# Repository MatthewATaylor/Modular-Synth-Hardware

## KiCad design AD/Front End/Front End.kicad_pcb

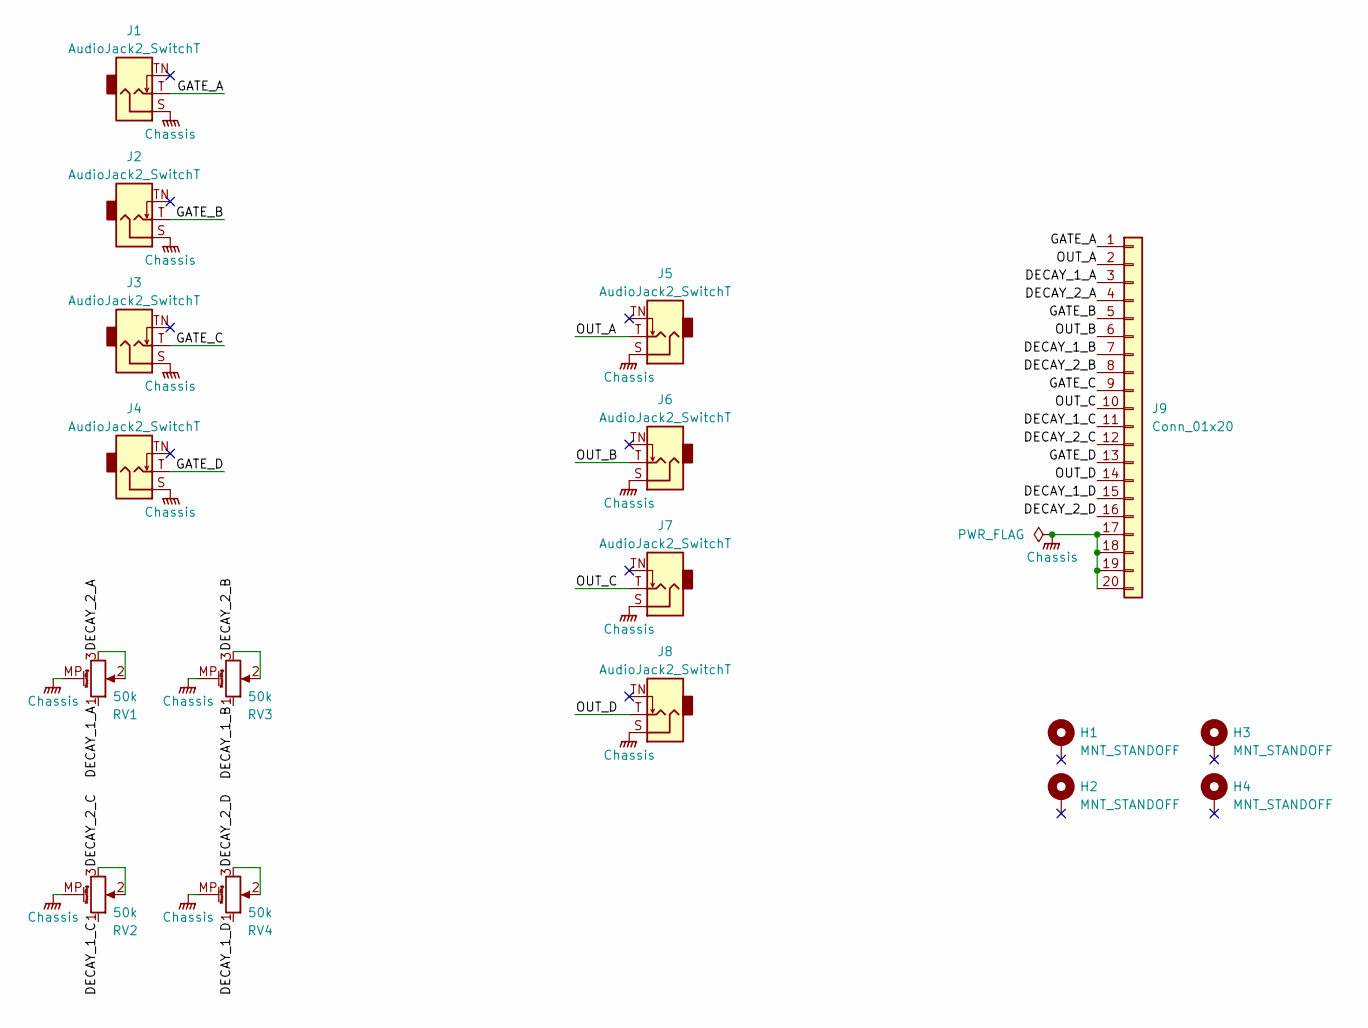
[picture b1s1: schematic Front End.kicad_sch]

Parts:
H1, H2, H3, H4: MNT_STANDOFF; MountingHole_Pitch7.5mm_Drill3.4mm
J1, J2, J3, J4, J5, J6, J7, J8: AudioJack2_SwitchT; Jack_3.5mm_QingPu_WQP-PJ398SM_Vertical_CircularHoles
J9: Conn_01x20; PinSocket_1x20_P2.54mm_Vertical
RV1, RV2, RV3, RV4: 50k; Potentiometer_Alpha_RD901F-40-00D_Single_Vertical_MP

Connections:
/DECAY_1_A: J9.3, RV1.1
/DECAY_1_B: J9.7, RV3.1
/DECAY_1_C: J9.11, RV2.1
/DECAY_1_D: J9.15, RV4.1
/DECAY_2_A: J9.4, RV1.2, RV1.3
/DECAY_2_B: J9.8, RV3.2, RV3.3
/DECAY_2_C: J9.12, RV2.2, RV2.3
/DECAY_2_D: J9.16, RV4.2, RV4.3
/GATE_A: J1.T, J9.1
/GATE_B: J2.T, J9.5
/GATE_C: J3.T, J9.9
/GATE_D: J4.T, J9.13
/OUT_A: J5.T, J9.2
/OUT_B: J6.T, J9.6
/OUT_C: J7.T, J9.10
/OUT_D: J8.T, J9.14
Chassis: J1.S, J2.S, J3.S, J4.S, J5.S, J6.S, J7.S, J8.S, J9.17, J9.18, J9.19, J9.20, RV1.MP (MountPin), RV2.MP (MountPin), RV3.MP (MountPin), RV4.MP (MountPin)

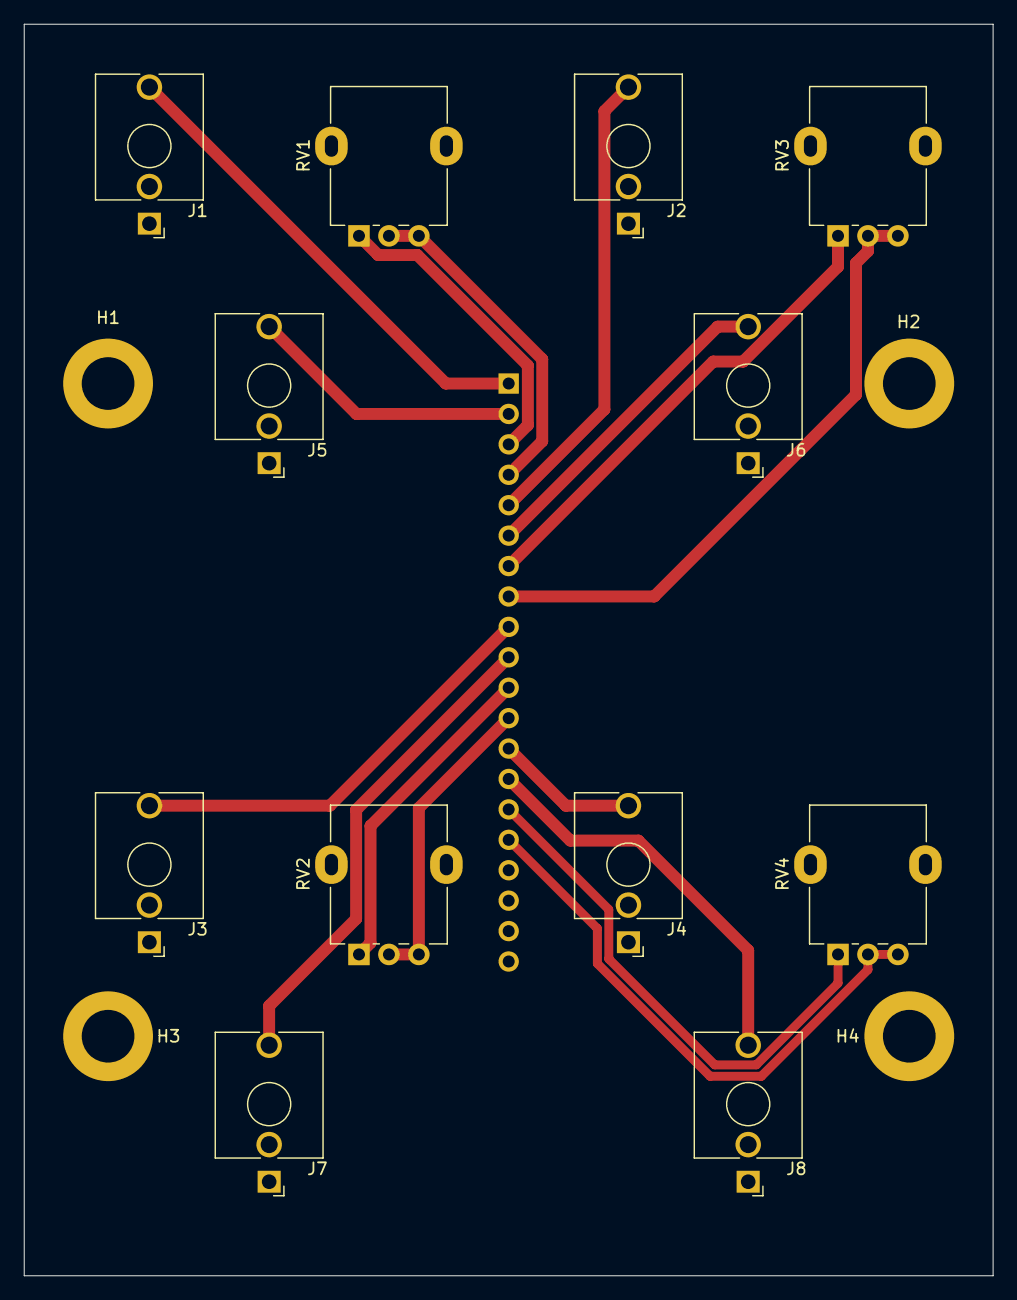
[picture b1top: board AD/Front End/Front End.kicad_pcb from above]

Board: 2 copper layers, 80.9 x 104.5 mm, 17 parts (1 on the bottom side), 17 nets.

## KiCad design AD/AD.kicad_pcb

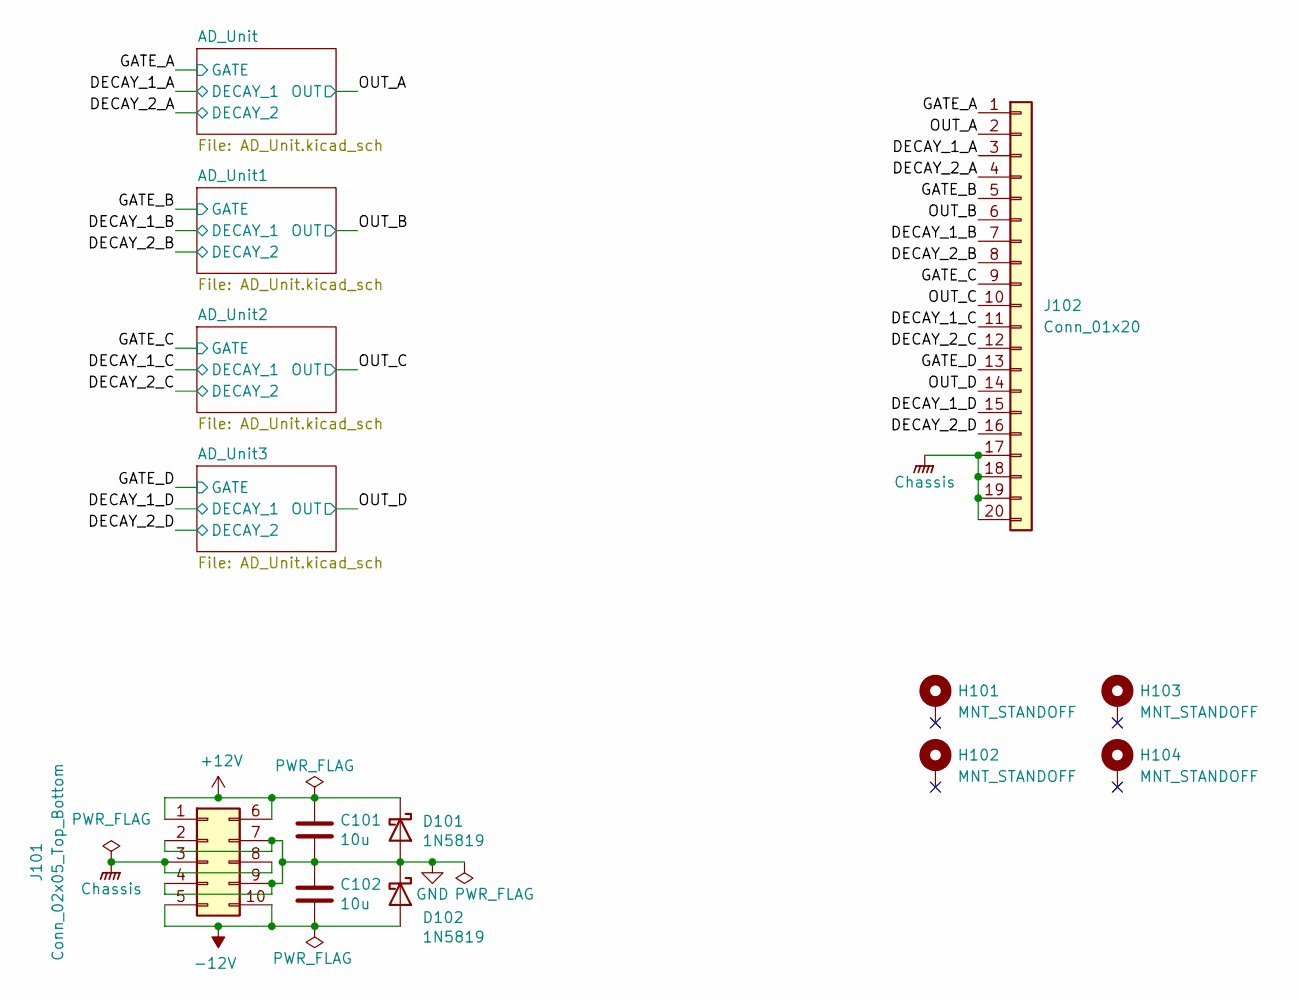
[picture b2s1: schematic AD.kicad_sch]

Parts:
C101, C102: 10u; C_Disc_D5.5mm_W4.0mm_P2.50mm
D101, D102: 1N5819; D_DO-41_SOD81_P10.16mm_Horizontal
H101, H102, H103, H104: MNT_STANDOFF; MountingHole_Pitch7.5mm_Drill3.4mm
J101: Conn_02x05_Top_Bottom; Molex_Mini-Fit_Jr_5566-10A_2x05_P4.20mm_Vertical
J102: Conn_01x20; PinHeader_1x20_P2.54mm_Vertical

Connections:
+12V: C101.1, D101.1 (K), J101.1, J101.6; also elsewhere on the board
-12V: C102.2, D102.2 (A), J101.5, J101.10
/DECAY_1_A: J102.3; also elsewhere on the board
/DECAY_1_B: J102.7; also elsewhere on the board
/DECAY_1_C: J102.11; also elsewhere on the board
/DECAY_1_D: J102.15; also elsewhere on the board
/DECAY_2_A: J102.4; also elsewhere on the board
/DECAY_2_B: J102.8; also elsewhere on the board
/DECAY_2_C: J102.12; also elsewhere on the board
/DECAY_2_D: J102.16; also elsewhere on the board
/GATE_A: J102.1; also elsewhere on the board
/GATE_B: J102.5; also elsewhere on the board
/GATE_C: J102.9; also elsewhere on the board
/GATE_D: J102.13; also elsewhere on the board
/OUT_A: J102.2; also elsewhere on the board
/OUT_B: J102.6; also elsewhere on the board
/OUT_C: J102.10; also elsewhere on the board
/OUT_D: J102.14; also elsewhere on the board
Chassis: J101.3, J101.8, J102.17, J102.18, J102.19, J102.20
GND: C101.2, C102.1, D101.2 (A), D102.1 (K), J101.2, J101.4, J101.7, J101.9; also elsewhere on the board

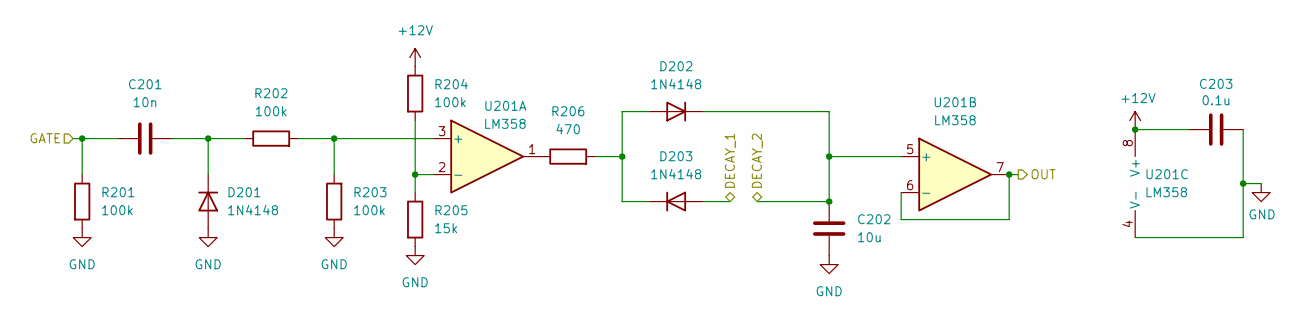
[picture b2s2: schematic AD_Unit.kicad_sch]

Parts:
C201: 10n; C_Disc_D5.5mm_W2.5mm_P2.50mm
C202: 10u; C_Disc_D5.5mm_W4.0mm_P2.50mm
C203: 0.1u; C_Disc_D5.5mm_W2.5mm_P2.50mm
D201, D202, D203: 1N4148; D_DO-35_SOD27_P7.62mm_Horizontal
R201, R202, R203, R204: 100k; R_Axial_DIN0207_L6.3mm_D2.5mm_P7.62mm_Horizontal
R205: 15k; R_Axial_DIN0207_L6.3mm_D2.5mm_P7.62mm_Horizontal
R206: 470; R_Axial_DIN0207_L6.3mm_D2.5mm_P7.62mm_Horizontal
U201: LM358; DIP-8_W7.62mm_Socket

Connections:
+12V: C203.1, R204.1, U201.8 (V+); also elsewhere on the board
/DECAY_1_A: D203.2 (A); also elsewhere on the board
/DECAY_2_A: C202.1, D202.1 (K), U201.5 (+); also elsewhere on the board
/GATE_A: C201.1, R201.1; also elsewhere on the board
/OUT_A: U201.6 (-), U201.7; also elsewhere on the board
GND: C202.2, C203.2, D201.2 (A), R201.2, R203.1, R205.2, U201.4 (V-); also elsewhere on the board
unnamed: C201.2, D201.1 (K), R202.1
unnamed: D202.2 (A), D203.1 (K), R206.2
unnamed: R206.1, U201.1
unnamed: R202.2, R203.2, U201.3 (+)
unnamed: R204.2, R205.1, U201.2 (-)

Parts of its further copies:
C401, C701, C901: 10n; C_Disc_D5.5mm_W2.5mm_P2.50mm
C402, C702, C902: 10u; C_Disc_D5.5mm_W4.0mm_P2.50mm
C403, C703, C903: 0.1u; C_Disc_D5.5mm_W2.5mm_P2.50mm
D401, D402, D403, D701, D702, D703, D901, D902, D903: 1N4148; D_DO-35_SOD27_P7.62mm_Horizontal
R401, R402, R403, R404, R701, R702, R703, R704, R901, R902, R903, R904: 100k; R_Axial_DIN0207_L6.3mm_D2.5mm_P7.62mm_Horizontal
R405, R705, R905: 15k; R_Axial_DIN0207_L6.3mm_D2.5mm_P7.62mm_Horizontal
R406, R706, R906: 470; R_Axial_DIN0207_L6.3mm_D2.5mm_P7.62mm_Horizontal
U401, U701, U901: LM358; DIP-8_W7.62mm_Socket

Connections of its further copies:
+12V: C403.1, C703.1, C903.1, R404.1, R704.1, R904.1, U401.8 (V+), U701.8 (V+), U901.8 (V+); also elsewhere on the board
/DECAY_1_B: D403.2 (A); also elsewhere on the board
/DECAY_1_C: D703.2 (A); also elsewhere on the board
/DECAY_1_D: D903.2 (A); also elsewhere on the board
/DECAY_2_B: C402.1, D402.1 (K), U401.5 (+); also elsewhere on the board
/DECAY_2_C: C702.1, D702.1 (K), U701.5 (+); also elsewhere on the board
/DECAY_2_D: C902.1, D902.1 (K), U901.5 (+); also elsewhere on the board
/GATE_B: C401.1, R401.1; also elsewhere on the board
/GATE_C: C701.1, R701.1; also elsewhere on the board
/GATE_D: C901.1, R901.1; also elsewhere on the board
/OUT_B: U401.6 (-), U401.7; also elsewhere on the board
/OUT_C: U701.6 (-), U701.7; also elsewhere on the board
/OUT_D: U901.6 (-), U901.7; also elsewhere on the board
GND: C402.2, C403.2, C702.2, C703.2, C902.2, C903.2, D401.2 (A), D701.2 (A), D901.2 (A), R401.2, R403.1, R405.2, R701.2, R703.1, R705.2, R901.2, R903.1, R905.2, U401.4 (V-), U701.4 (V-), U901.4 (V-); also elsewhere on the board
unnamed: C401.2, D401.1 (K), R402.1
unnamed: D402.2 (A), D403.1 (K), R406.2
unnamed: C701.2, D701.1 (K), R702.1
unnamed: D702.2 (A), D703.1 (K), R706.2
unnamed: C901.2, D901.1 (K), R902.1
unnamed: D902.2 (A), D903.1 (K), R906.2
unnamed: R406.1, U401.1
unnamed: R706.1, U701.1
unnamed: R906.1, U901.1
unnamed: R402.2, R403.2, U401.3 (+)
unnamed: R404.2, R405.1, U401.2 (-)
unnamed: R702.2, R703.2, U701.3 (+)
unnamed: R704.2, R705.1, U701.2 (-)
unnamed: R902.2, R903.2, U901.3 (+)
unnamed: R904.2, R905.1, U901.2 (-)

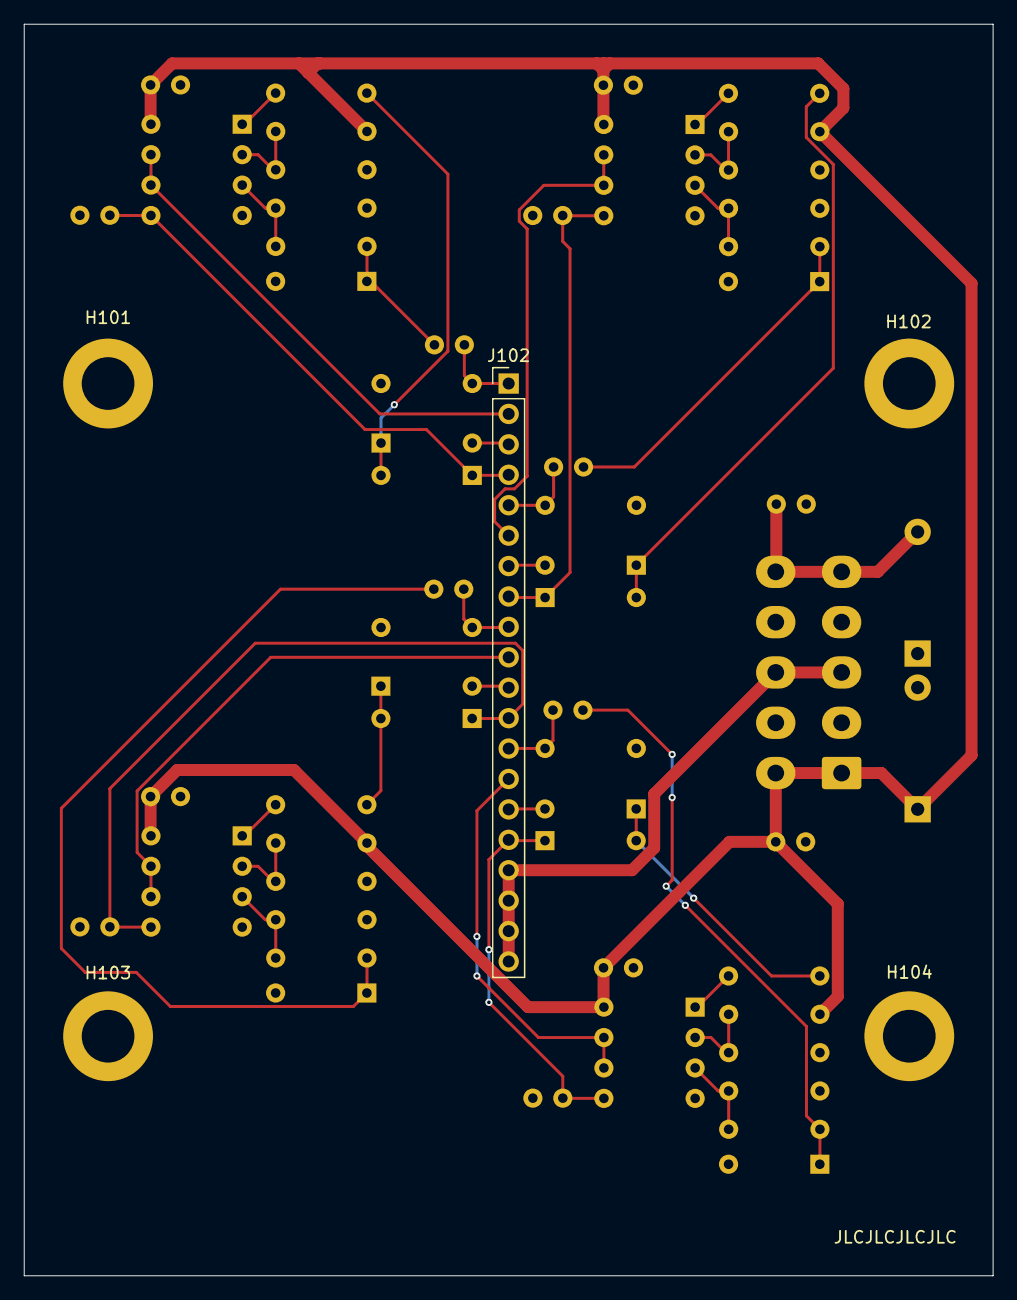
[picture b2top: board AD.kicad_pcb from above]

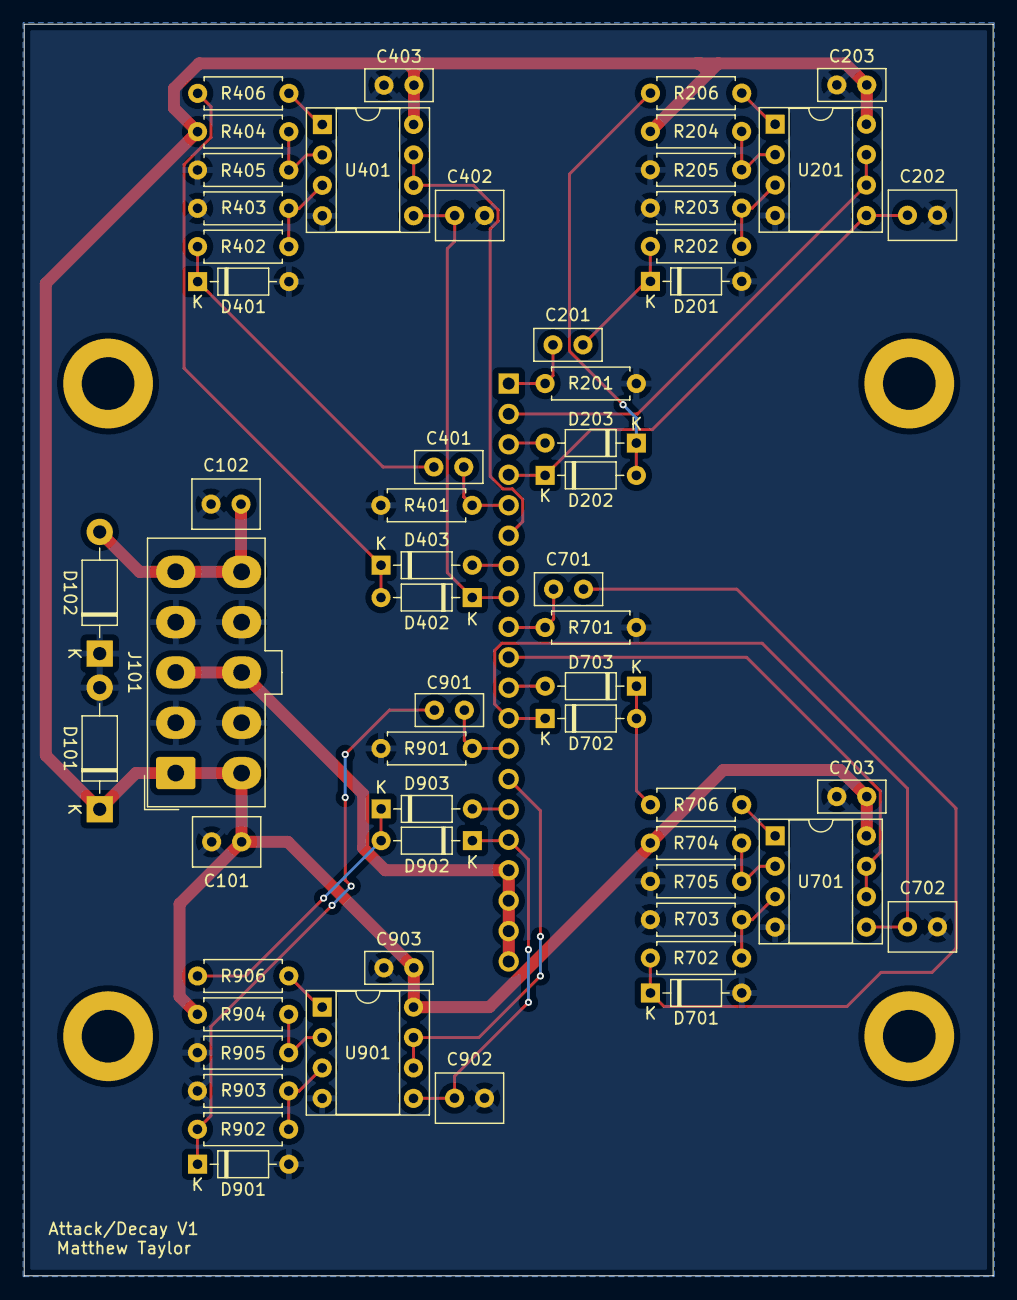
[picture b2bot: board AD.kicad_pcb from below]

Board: 2 copper layers, 80.9 x 104.5 mm, 62 parts (57 on the bottom side), 40 nets.

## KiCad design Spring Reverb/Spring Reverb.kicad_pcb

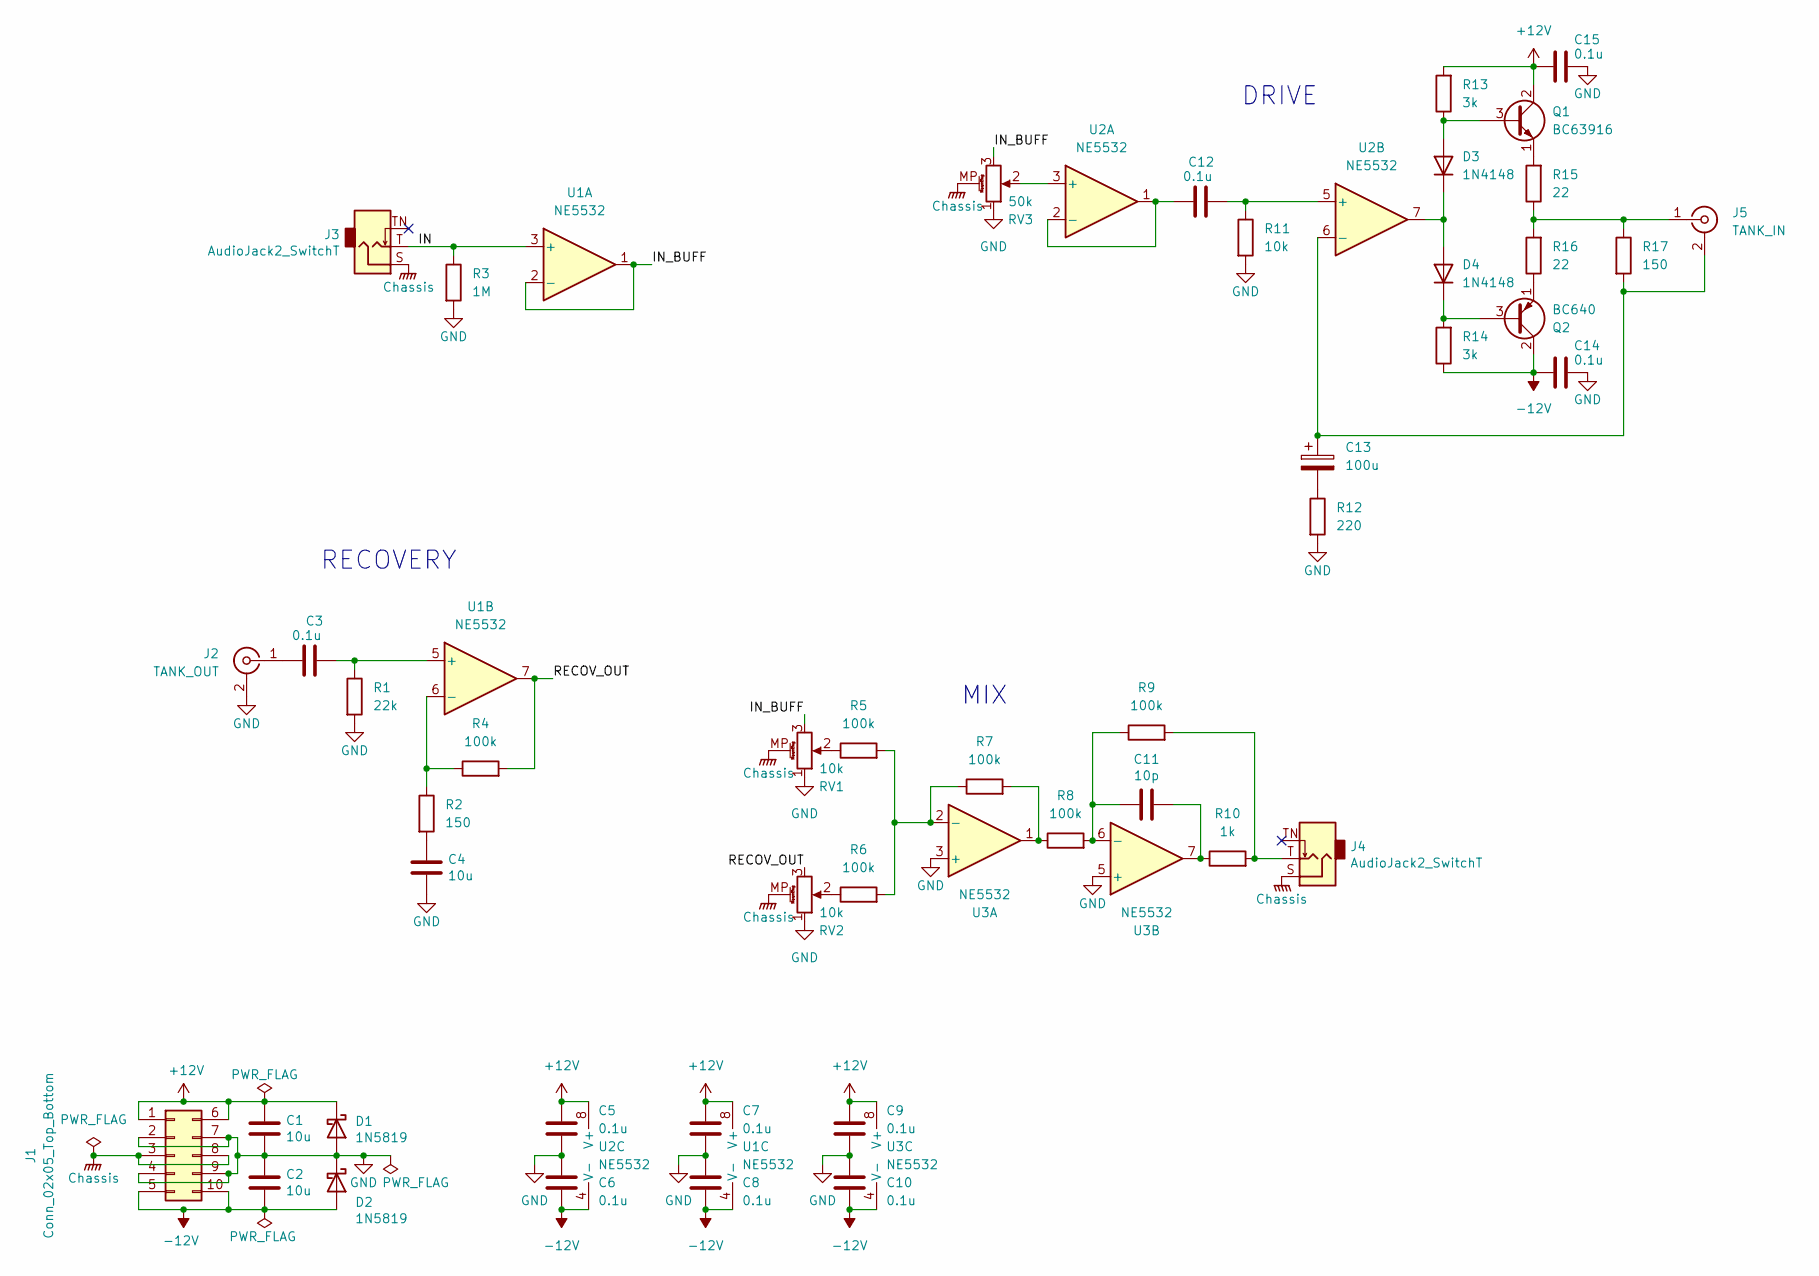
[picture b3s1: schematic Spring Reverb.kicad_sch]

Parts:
C1, C2, C4: 10u; C_Disc_D5.5mm_W4.0mm_P2.50mm
C3, C5, C6, C7, C8, C9, C10, C12, C14, C15: 0.1u; C_Disc_D5.5mm_W2.5mm_P2.50mm
C11: 10p; C_Disc_D5.5mm_W2.5mm_P2.50mm
C13: 100u; CP_Radial_D6.3mm_P2.50mm
D1, D2: 1N5819; D_DO-41_SOD81_P10.16mm_Horizontal
D3, D4: 1N4148; D_DO-35_SOD27_P7.62mm_Horizontal
J1: Conn_02x05_Top_Bottom; Molex_Mini-Fit_Jr_5566-10A_2x05_P4.20mm_Vertical
J2: TANK_OUT; RCA_KLPX-0848-2
J3, J4: AudioJack2_SwitchT; Jack_3.5mm_QingPu_WQP-PJ398SM_Vertical_CircularHoles
J5: TANK_IN; RCA_KLPX-0848-2
Q1: BC63916; TO-92_HandSolder
Q2: BC640; TO-92_HandSolder
R1: 22k; R_Axial_DIN0207_L6.3mm_D2.5mm_P7.62mm_Horizontal
R2, R17: 150; R_Axial_DIN0207_L6.3mm_D2.5mm_P7.62mm_Horizontal
R3: 1M; R_Axial_DIN0207_L6.3mm_D2.5mm_P7.62mm_Horizontal
R4, R5, R6, R7, R8, R9: 100k; R_Axial_DIN0207_L6.3mm_D2.5mm_P7.62mm_Horizontal
R10: 1k; R_Axial_DIN0207_L6.3mm_D2.5mm_P7.62mm_Horizontal
R11: 10k; R_Axial_DIN0207_L6.3mm_D2.5mm_P7.62mm_Horizontal
R12: 220; R_Axial_DIN0207_L6.3mm_D2.5mm_P7.62mm_Horizontal
R13, R14: 3k; R_Axial_DIN0207_L6.3mm_D2.5mm_P7.62mm_Horizontal
R15, R16: 22; R_Axial_DIN0207_L6.3mm_D2.5mm_P7.62mm_Horizontal
RV1, RV2: 10k; Potentiometer_Alpha_RD901F-40-00D_Single_Vertical_MP
RV3: 50k; Potentiometer_Alpha_RD901F-40-00D_Single_Vertical_MP
U1, U2, U3: NE5532; DIP-8_W7.62mm_Socket

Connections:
+12V: C1.1, C5.2, C7.2, C9.2, C15.1, D1.1 (K), J1.1, J1.6, Q1.2 (C), R13.2, U1.8 (V+), U2.8 (V+), U3.8 (V+)
-12V: C2.2, C6.1, C8.1, C10.1, C14.1, D2.2 (A), J1.5, J1.10, Q2.2 (C), R14.1, U1.4 (V-), U2.4 (V-), U3.4 (V-)
/IN: J3.T, R3.1, U1.3 (+)
/IN_BUFF: RV1.3, RV3.3, U1.1, U1.2 (-)
/RECOV_OUT: R4.2, RV2.3, U1.7
Chassis: J1.3, J1.8, J3.S, J4.S, RV1.MP (MountPin), RV2.MP (MountPin), RV3.MP (MountPin)
GND: C1.2, C2.1, C4.2, C5.1, C6.2, C7.1, C8.2, C9.1, C10.2, C14.2, C15.2, D1.2 (A), D2.1 (K), J1.2, J1.4, J1.7, J1.9, J2.2 (Ext), R1.2, R3.2, R11.2, R12.2, RV1.1, RV2.1, RV3.1, U3.3 (+), U3.5 (+)
unnamed: C4.1, R2.2
unnamed: C11.2, R10.1, U3.7
unnamed: C13.2, R12.1
unnamed: D3.2 (A), Q1.3 (B), R13.1
unnamed: D3.1 (K), D4.2 (A), U2.7
unnamed: D4.1 (K), Q2.3 (B), R14.2
unnamed: C3.2, J2.1 (In)
unnamed: J4.T, R9.2, R10.2
unnamed: C13.1, J5.2 (Ext), R17.2, U2.6 (-)
unnamed: J5.1 (In), R15.1, R16.2, R17.1
unnamed: Q1.1 (E), R15.2
unnamed: Q2.1 (E), R16.1
unnamed: R5.1, RV1.2
unnamed: R6.1, RV2.2
unnamed: R7.2, R8.1, U3.1
unnamed: C3.1, R1.1, U1.5 (+)
unnamed: R2.1, R4.1, U1.6 (-)
unnamed: RV3.2, U2.3 (+)
unnamed: C12.2, U2.1, U2.2 (-)
unnamed: C12.1, R11.1, U2.5 (+)
unnamed: R5.2, R6.2, R7.1, U3.2 (-)
unnamed: C11.1, R8.2, R9.1, U3.6 (-)

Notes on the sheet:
RECOVERY
DRIVE
MIX

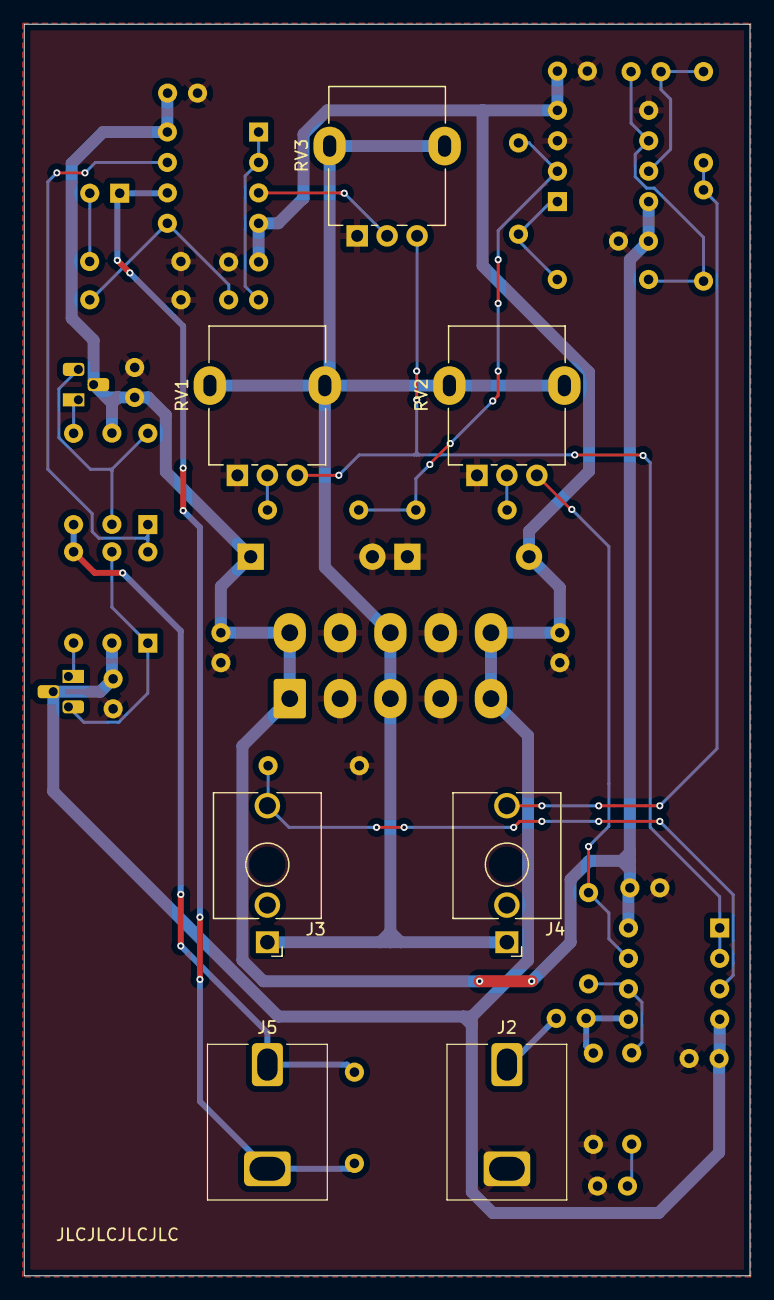
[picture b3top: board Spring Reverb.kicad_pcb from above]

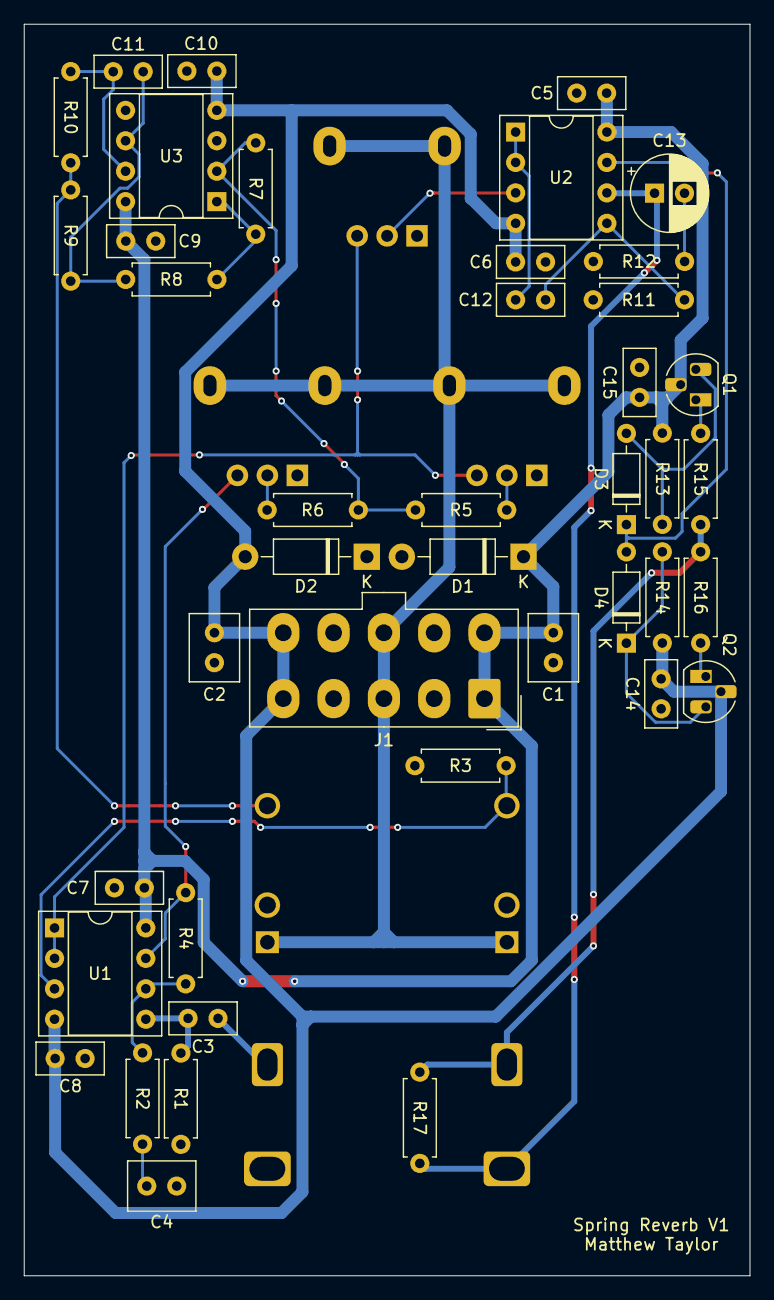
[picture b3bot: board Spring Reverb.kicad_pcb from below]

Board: 2 copper layers, 60.6 x 104.5 mm, 49 parts (42 on the bottom side), 29 nets.

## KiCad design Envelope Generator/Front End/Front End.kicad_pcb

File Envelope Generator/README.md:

# Envelope Generator

An ADSR envelope generator based on [René Schmitz's 555 timer ADSR design](https://www.schmitzbits.de/adsr.html), including two normal outputs and two inverted outputs.

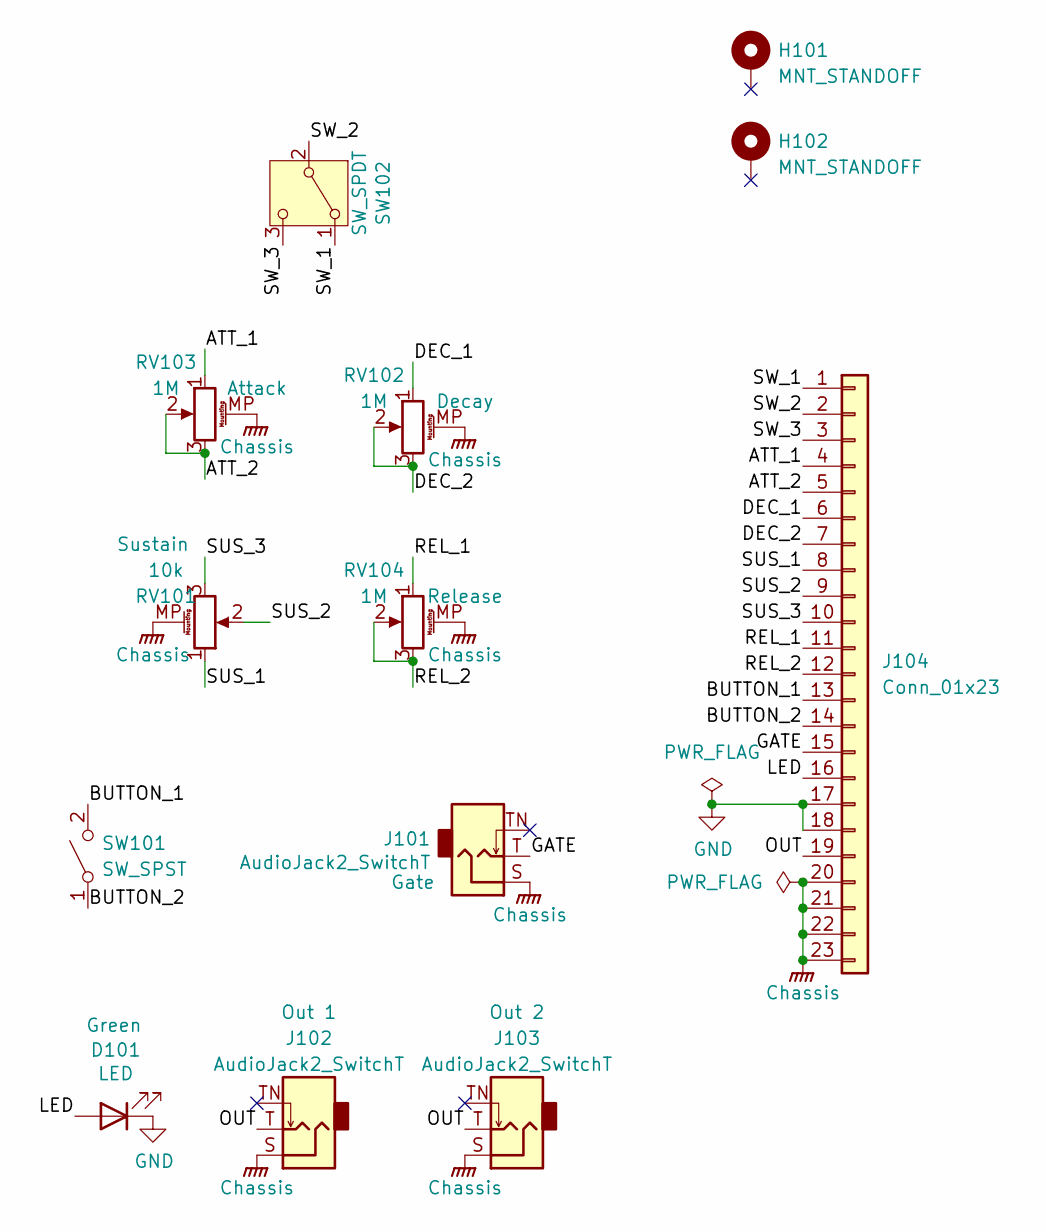
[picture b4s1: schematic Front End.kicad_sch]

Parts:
D101: LED; LED_D5.0mm
H101, H102: MNT_STANDOFF; MountingHole_Pitch7.5mm_Drill3.4mm
J101, J102, J103: AudioJack2_SwitchT; Jack_3.5mm_QingPu_WQP-PJ398SM_Vertical_CircularHoles
J104: Conn_01x23; PinHeader_1x23_P2.54mm_Vertical
RV101: 10k; Potentiometer_Alpha_RD901F-40-00D_Single_Vertical_MP
RV102, RV103, RV104: 1M; Potentiometer_Alpha_RD901F-40-00D_Single_Vertical_MP
SW101: SW_SPST; PBS-105
SW102: SW_SPDT; MTS-102_MTS-103_MTS-112_MTS-113_MTS-123

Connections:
/ATT_1: J104.4, RV103.1
/ATT_2: J104.5, RV103.2, RV103.3
/BUTTON_1: J104.13, SW101.2 (B)
/BUTTON_2: J104.14, SW101.1 (A)
/DEC_1: J104.6, RV102.1
/DEC_2: J104.7, RV102.2, RV102.3
/GATE: J101.T, J104.15
/LED: D101.2 (A), J104.16
/OUT: J102.T, J103.T, J104.19
/REL_1: J104.11, RV104.1
/REL_2: J104.12, RV104.2, RV104.3
/SUS_1: J104.8, RV101.1
/SUS_2: J104.9, RV101.2
/SUS_3: J104.10, RV101.3
/SW_1: J104.1, SW102.1 (A)
/SW_2: J104.2, SW102.2 (B)
/SW_3: J104.3, SW102.3 (C)
Chassis: J101.S, J102.S, J103.S, J104.20, J104.21, J104.22, J104.23, RV101.MP (MountPin), RV102.MP (MountPin), RV103.MP (MountPin), RV104.MP (MountPin)
GND: D101.1 (K), J104.17, J104.18

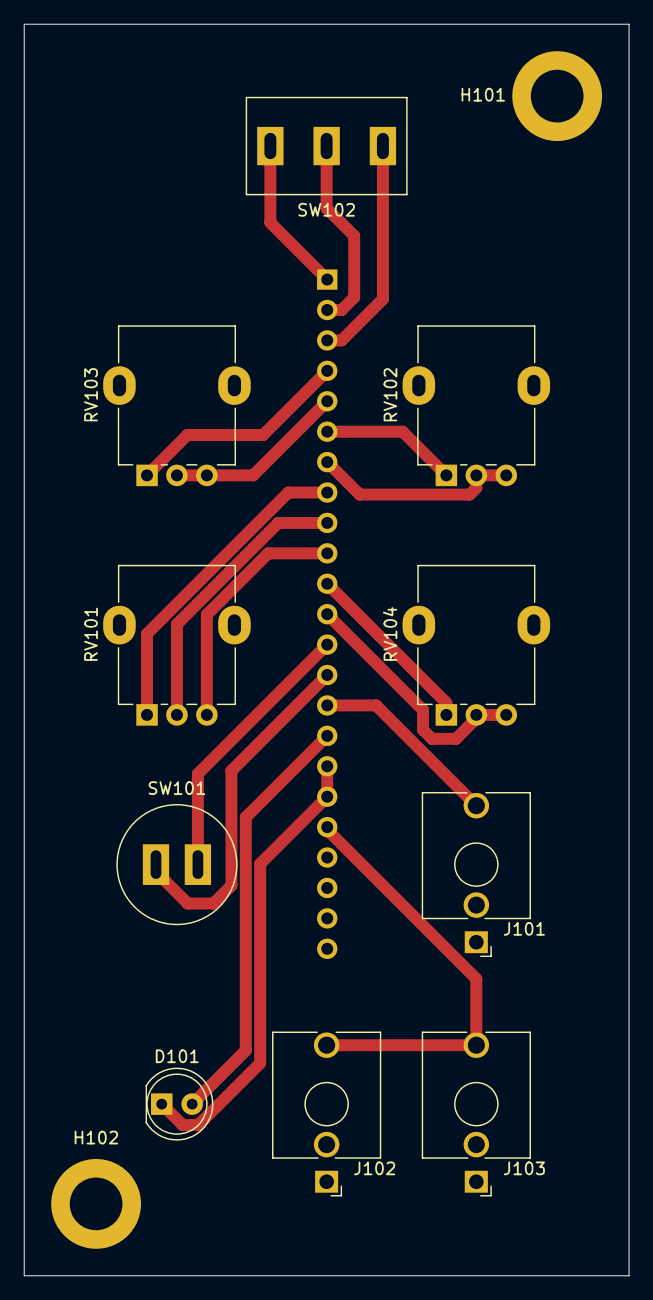
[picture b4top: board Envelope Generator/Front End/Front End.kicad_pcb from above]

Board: 2 copper layers, 50.5 x 104.5 mm, 13 parts (1 on the bottom side), 19 nets.

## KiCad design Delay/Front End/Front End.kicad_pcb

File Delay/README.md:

# Delay

A triple PT2399 delay module, including individual and master delay time CV and daisy chaining controls.

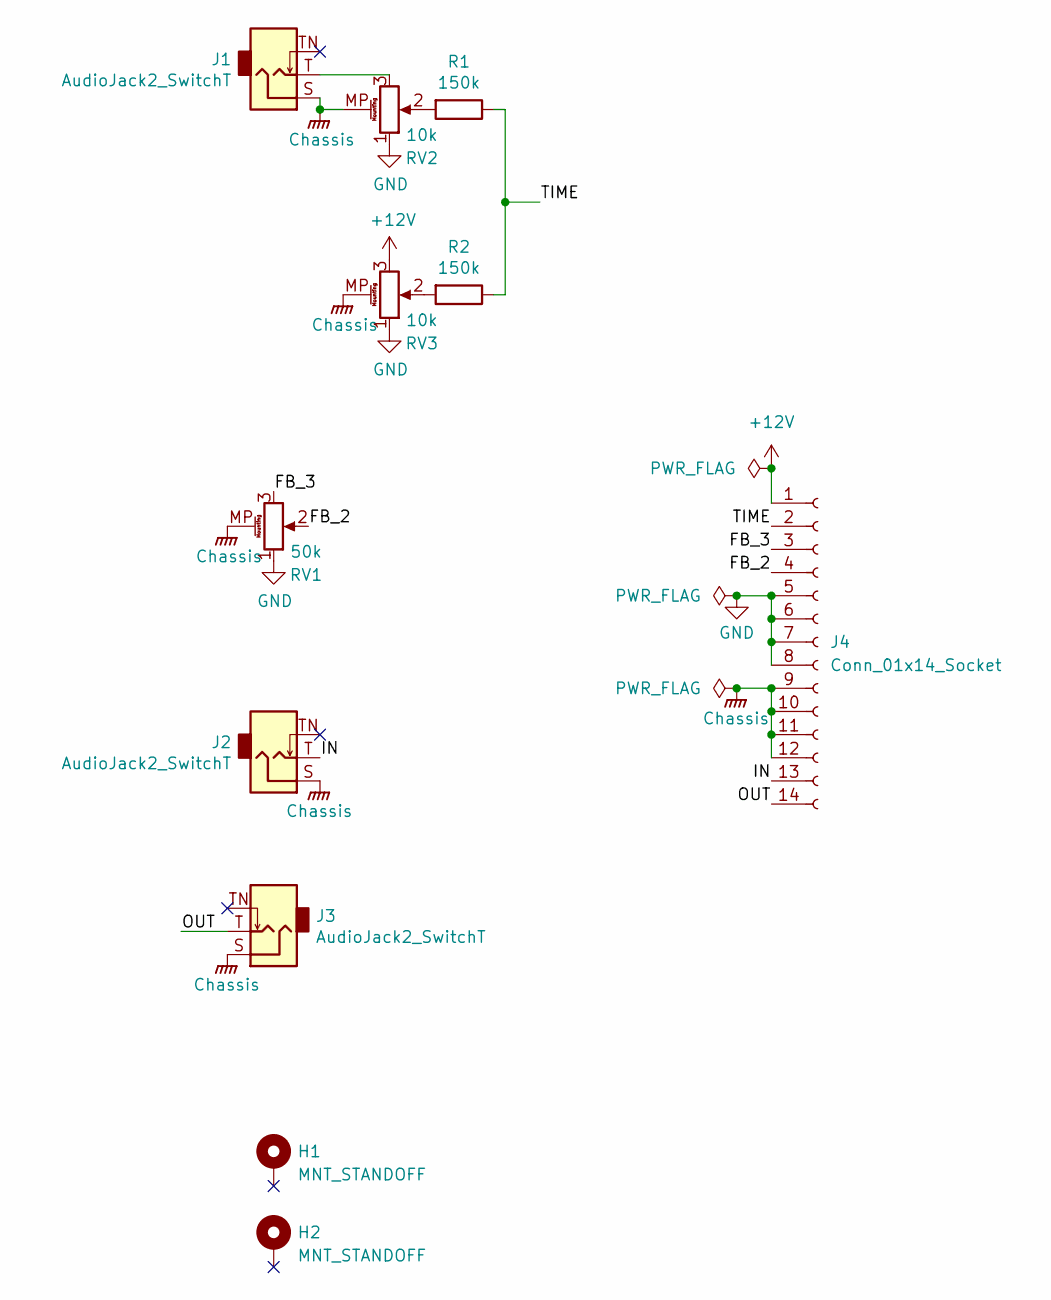
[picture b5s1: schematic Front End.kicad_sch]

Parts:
H1, H2: MNT_STANDOFF; MountingHole_Pitch7.5mm_Drill3.4mm
J1, J2, J3: AudioJack2_SwitchT; Jack_3.5mm_QingPu_WQP-PJ398SM_Vertical_CircularHoles
J4: Conn_01x14_Socket; PinHeader_1x14_P2.54mm_Vertical
R1, R2: 150k; R_Axial_DIN0207_L6.3mm_D2.5mm_P7.62mm_Horizontal
RV1: 50k; Potentiometer_Alpha_RD901F-40-00D_Single_Vertical_MP
RV2, RV3: 10k; Potentiometer_Alpha_RD901F-40-00D_Single_Vertical_MP

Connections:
+12V: J4.1, RV3.3
/FB_2: J4.4, RV1.2
/FB_3: J4.3, RV1.3
/IN: J2.T, J4.13
/OUT: J3.T, J4.14
/TIME: J4.2, R1.1, R2.1
Chassis: J1.S, J2.S, J3.S, J4.9, J4.10, J4.11, J4.12, RV1.MP (MountPin), RV2.MP (MountPin), RV3.MP (MountPin)
GND: J4.5, J4.6, J4.7, J4.8, RV1.1, RV2.1, RV3.1
unnamed: J1.T, RV2.3
unnamed: R1.2, RV2.2
unnamed: R2.2, RV3.2

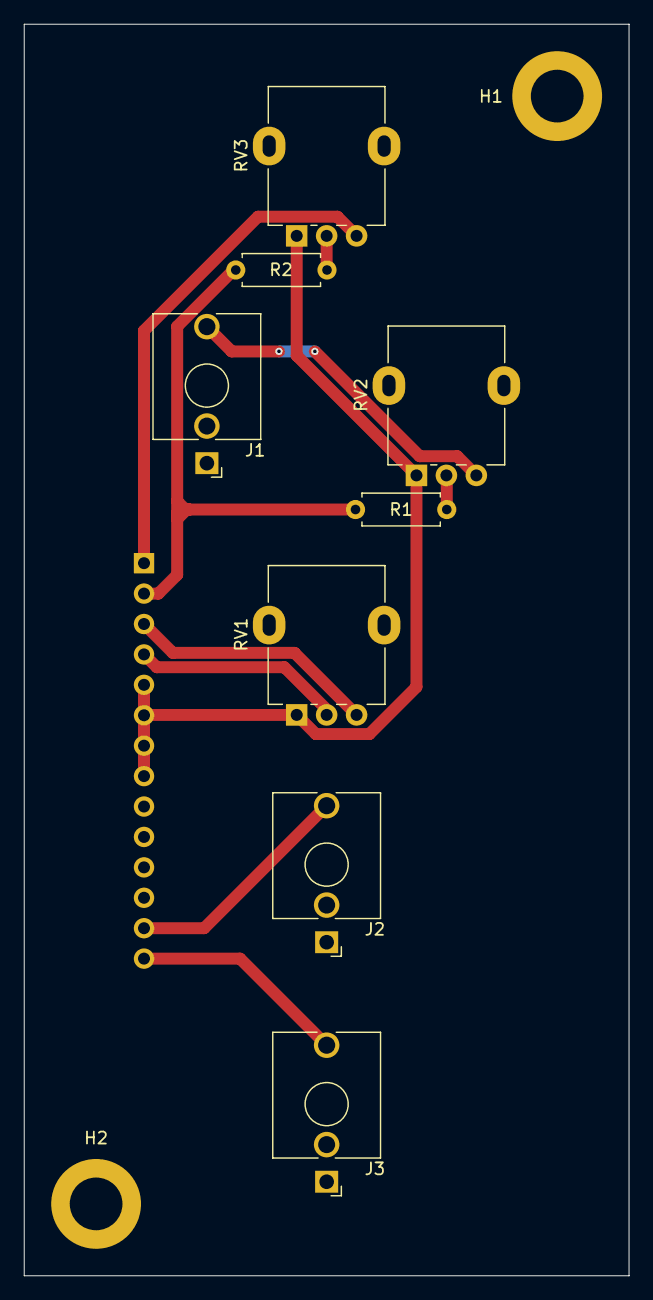
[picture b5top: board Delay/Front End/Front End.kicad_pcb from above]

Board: 2 copper layers, 50.5 x 104.5 mm, 11 parts (1 on the bottom side), 11 nets.
